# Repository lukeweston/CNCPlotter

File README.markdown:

CNCPlotter

The Freetronics CNCPlotter board is an Arduino-compatible embedded machine which incorporates two bipolar stepper motor drivers, suitable for CNC experiments and other
robotics and mechatronics applications.

The board incorporates the following hardware features:
 
- Atmel ATmega32U4 microcontroller, compatible with the Arduino Leonardo firmware, and USB connectivity to the PC. 
- 20x4 HD44780-compatible alphanumeric LCD display 
- Micro-SD card socket, for example usable for the execution of stored programs without connection to a PC. 
- Connector for a small (hobby RC aircraft style) servo motor 
- Two onboard DRV8811 bipolar stepper motor driver ICs 
- Inputs for three "limit" or "home" switches (or switches with any other kind of software-defined functionality!) 
- Connector for a cheap 4-wire resistive touchscreen, such as a Nintendo DS compatible touchscreen 
- Power supply input voltage range of 9-30V. (At least 1A current capacity is required to run the stepper motors.) 
- Output header for an optional third stepper motor driver IC, enabling three-axis CNC applications. 

Assuming you're using an Arduino Leonardo bootloader, the following is the mapping of Arduino pins to hardware functions.	

D0: UART RXD (not used, broken out to spare header) 	
D1: UART TXD (not used, broken out to spare header) 	
D2: LCD Strobe (Data loaded serially from AVR into 8-bit latch. Same as Pebble LCD hardware.) 	
D3: LCD Data 	
D4: LCD Clock 	
D5: Z-axis direction (not used in most cases) 	
D6: SD Card SPI chip select (active low). Standard SPI hardware (MOSI, MISO, SCK) used for SPI communications with SD card. 	
D7: Z-axis limit switch input (not used in most cases) 	
D8: Y-axis step signal 	
D9: Y-axis direction signal 	
D10: X-axis step signal 	
D11: X-axis direction signal 	
D12: Servo motor PWM position signal 	
D13: Z-axis step signal (not used usually) 	

A0: Touchscreen 1 	
A1: Touchscreen 2 	
A2: Touchscreen 3 	
A3: Touchscreen 4 	
A4: Y-axis limit switch input 	
A5: X-axis limit switch input

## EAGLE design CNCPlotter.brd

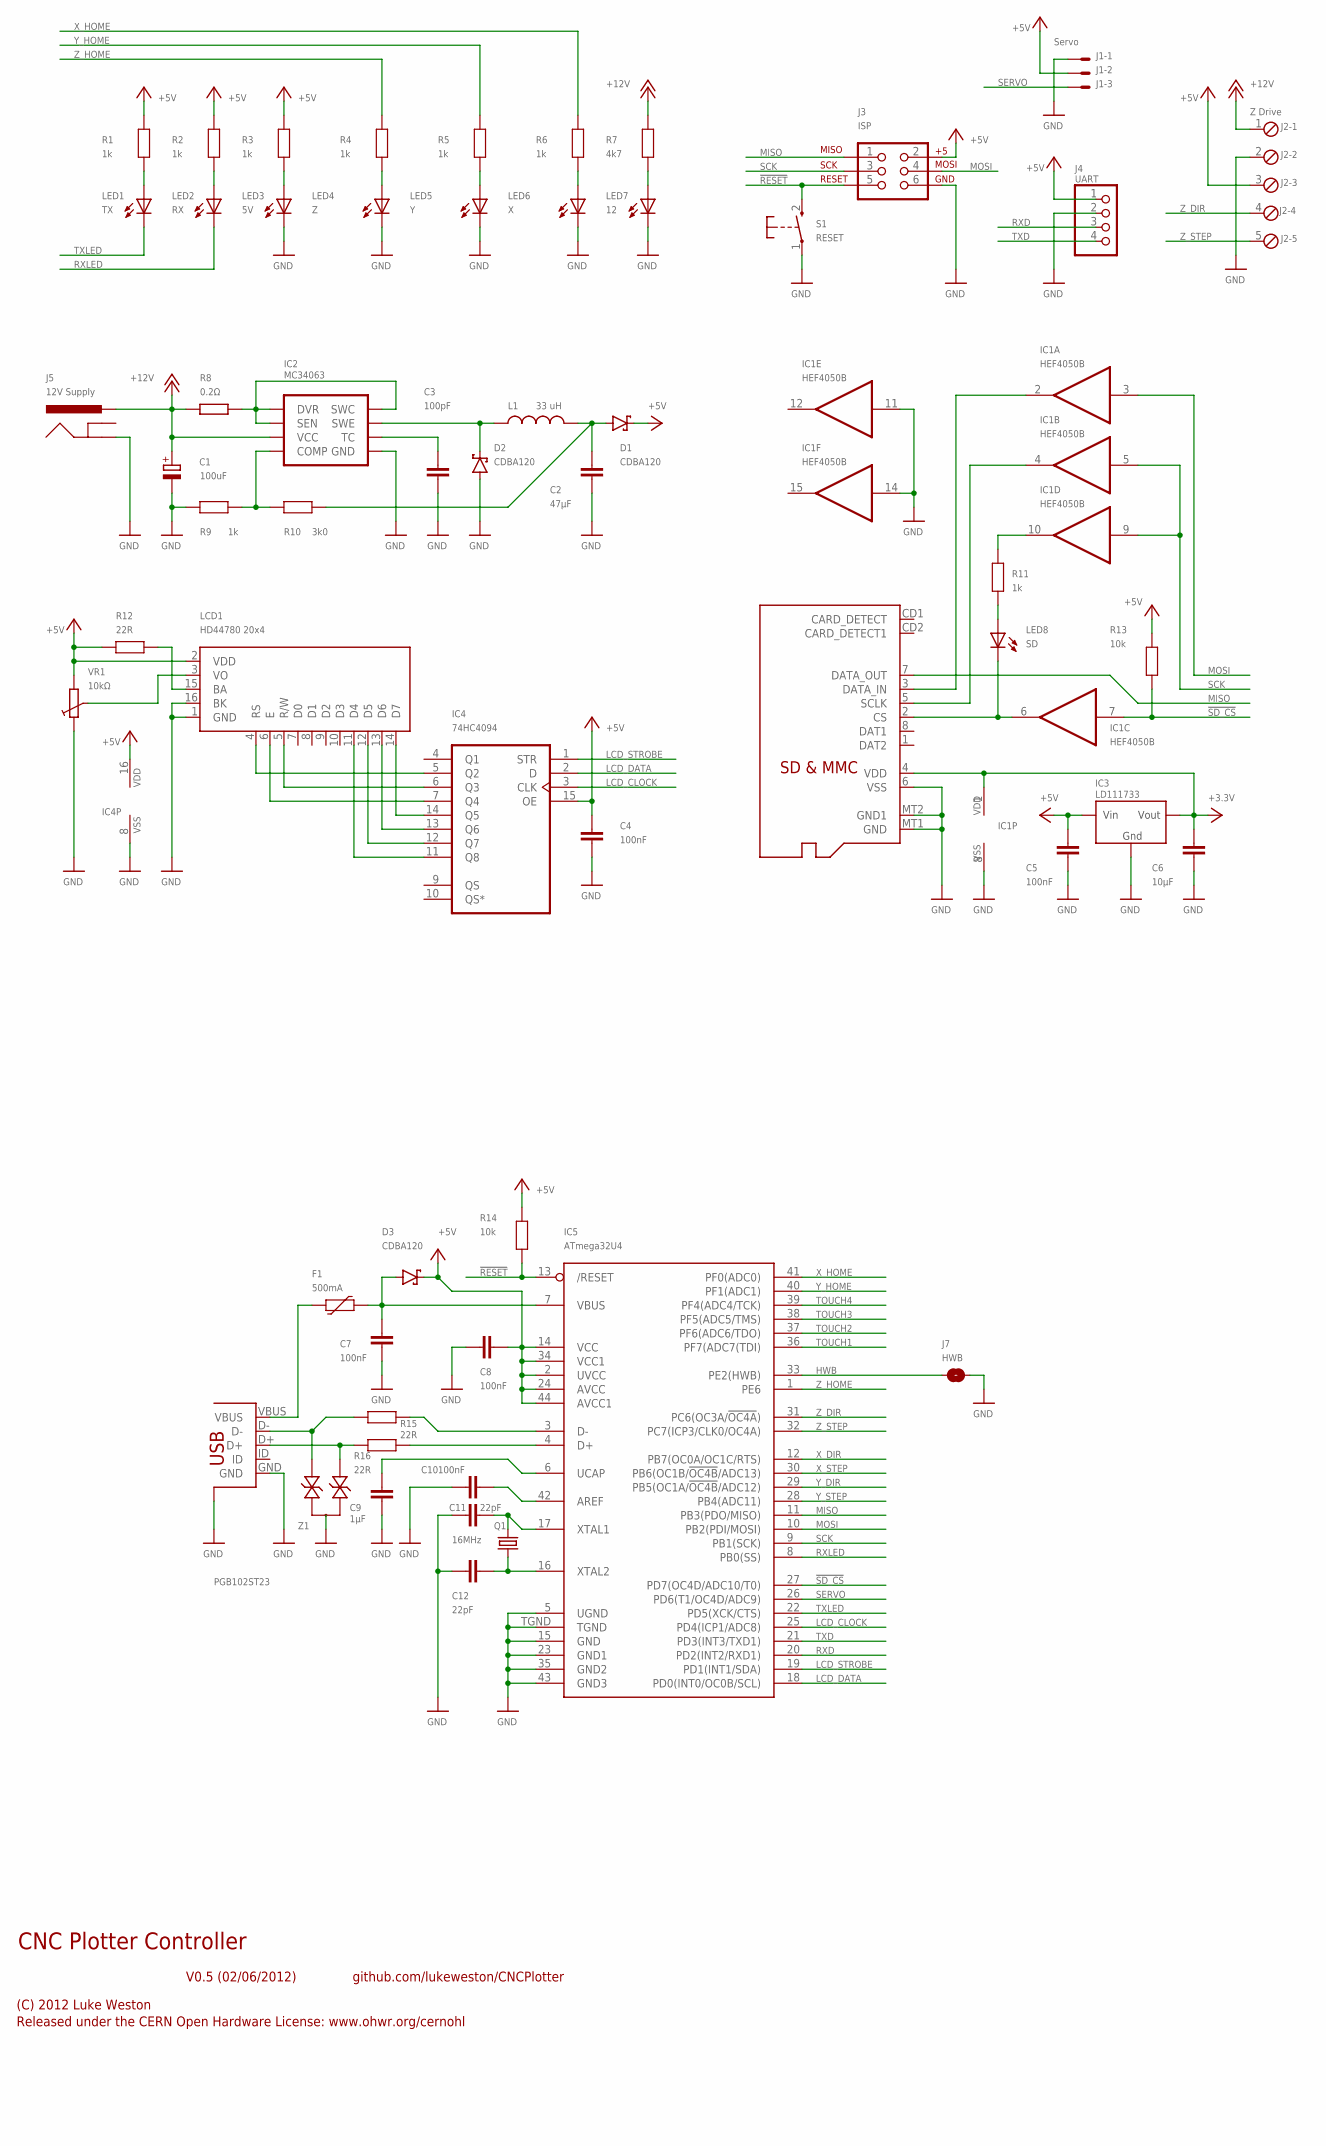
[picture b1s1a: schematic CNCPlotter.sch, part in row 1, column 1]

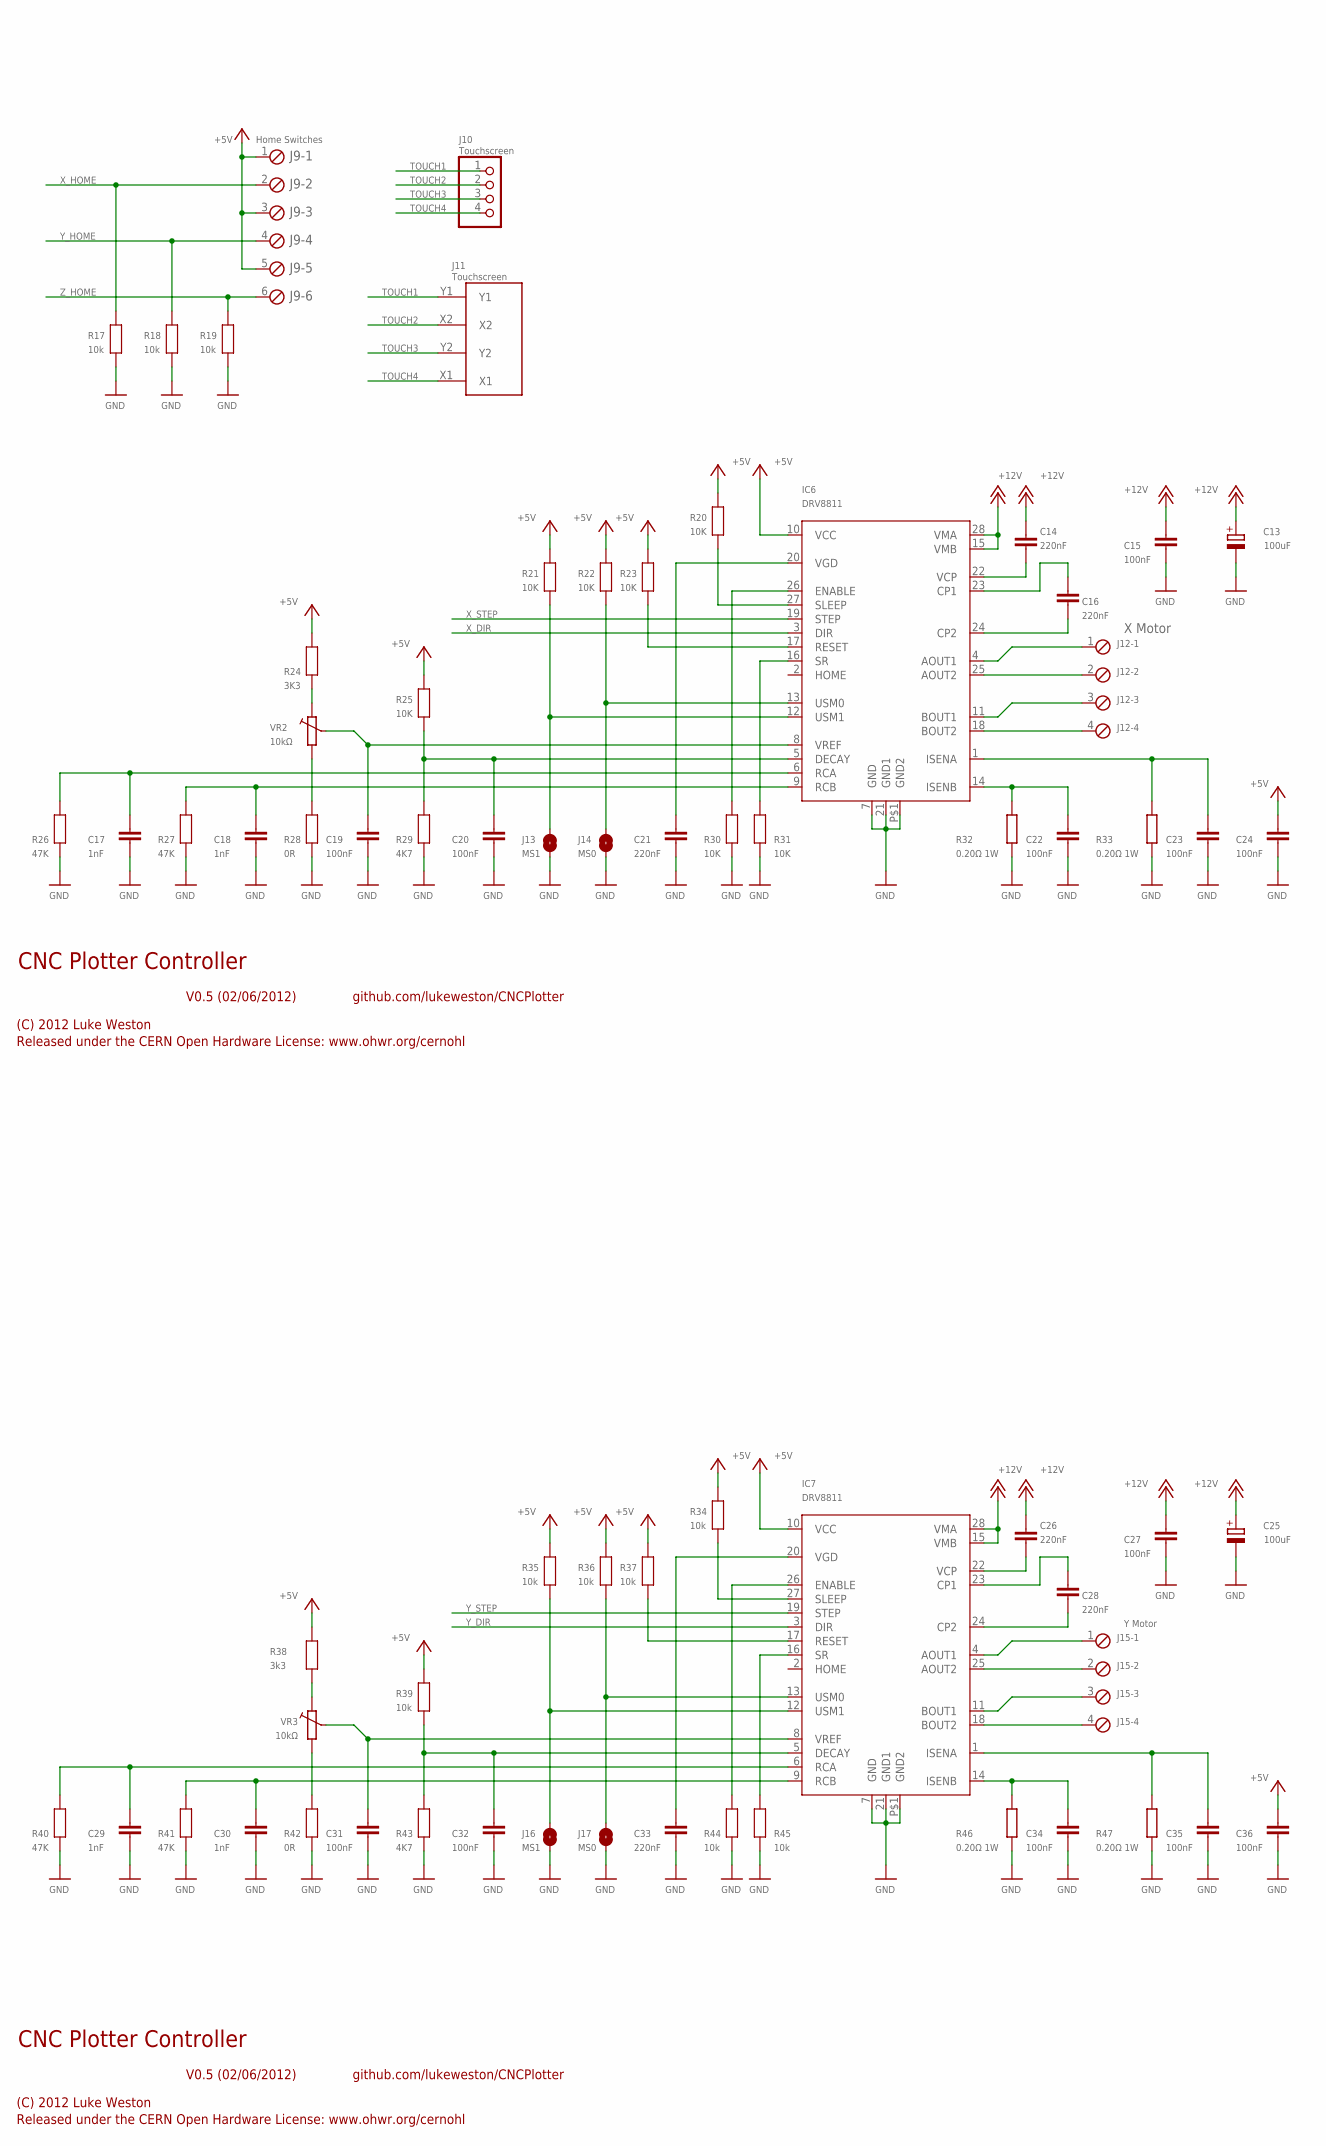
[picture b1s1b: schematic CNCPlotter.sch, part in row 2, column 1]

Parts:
C1, C13, C25: 100uF; E2,5-6
C2: 47µF; C1210
C3: 100pF; 0603
C4, C5, C7, C8, C10, C15, C19, C20, C22, C23, C24, C27, C31, C32, C34, C35, C36: 100nF; 0603
C6: 10µF; 0805
C9: 1µF; 0603
C11, C12: 22pF; 0603
C14, C16, C21, C26, C28, C33: 220nF; 0603
C17, C18, C29, C30: 1nF; 0603
D1, D2, D3: CDBA120; SMA
F1: 500mA; 1812
IC1: HEF4050B; SO16
IC2: MC34063; SO08
IC3: LD111733; SOT223
IC4: 74HC4094; SO16@1
IC5: ATmega32U4; QFN-44N
IC6, IC7: DRV8811; HTSSOP28
J1: Servo; 22-23-2031
J2: Z Drive; 5POL254
J3: ISP; 2X3-NS
J4: UART; 1X04
J5: 12V Supply; POWER_JACK_SLOT
J6: MicroSD Card; ADAFRUIT_MICROSD
J7: HWB; SJ
J8: USB; USB-MINIB-FT
J9: Home Switches; 6POL254
J10: Touchscreen; 1X04
J11: Touchscreen; DS_TOUCH_CONNECTOR
J12: X Motor; 4POL254
J13, J16: MS1; SJ
J14, J17: MS0; SJ
J15: Y Motor; 4POL254
L1: 33 uH; CR75
LCD1: HD44780 20x4; HDM20416L
LED1: TX; LED-0603
LED2: RX; LED-0603
LED3: 5V; LED-0603
LED4: Z; LED-0603
LED5: Y; LED-0603
LED6: X; LED-0603
LED7: 12; LED-0603
LED8: SD; LED-0603
Q1: 16MHz; HC49US
R1, R2, R3, R4, R5, R6, R9, R11: 1k; 0603
R7: 4k7; 0603
R8: 0.2Ω; R1210
R10: 3k0; 0603
R12, R15, R16: 22R; 0603
R13, R14, R17, R18, R19, R34, R35, R36, R37, R39, R44, R45: 10k; 0603
R20, R21, R22, R23, R25, R30, R31: 10K; 0603
R24: 3K3; 0603
R26, R27, R40, R41: 47K; 0603
R28, R42: 0R; 0603
R29, R43: 4K7; 0603
R32, R33, R46, R47: 0.20Ω 1W; R2010
R38: 3k3; 0603
S1: RESET; TACTILE_SWITCH_SMD_2PIN_TINY
VR1, VR2, VR3: 10kΩ; CT6
Z1: PGB102ST23; SOT23-3

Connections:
!RESET: IC5.13 (/RESET), J3.5, R14.1, S1.2 (S)
!SD_CS: IC1.7 (I), IC5.27 (PD7(OC4D/ADC10/T0)), R13.1
+5V: C4.1, C5.1, C8.2, C24.1, C36.1, D1.K, D3.K, IC3.3 (VIN), IC4.15 (OE), IC4.16 (VDD), IC5.2 (UVCC), IC5.14 (VCC), IC5.24 (AVCC), IC5.34 (VCC1), IC5.44 (AVCC1), IC6.10 (VCC), IC7.10 (VCC), J1.2, J2.3, J3.2, J4.1, J9.1, J9.3, J9.5, LCD1.2 (VDD), R1.2, R2.2, R3.2, R12.2, R13.2, R14.2, R20.2, R21.2, R22.2, R23.2, R24.2, R25.2, R34.2, R35.2, R36.2, R37.2, R38.2, R39.2, VR1.A
+12V: C1.+, C13.+, C14.1, C15.1, C25.+, C26.1, C27.1, IC2.6 (VCC), IC6.15 (VMB), IC6.28 (VMA), IC7.15 (VMB), IC7.28 (VMA), J2.1, J5.PWR, R7.2, R8.1
FOO: IC1.6 (O), J6.2 (CS), LED8.C
GND: C1.-, C2.2, C3.2, C4.2, C5.2, C6.2, C7.2, C8.1, C9.1, C10.1, C11.1, C12.1, C13.-, C15.2, C17.2, C18.2, C19.2, C20.2, C21.2, C22.2, C23.2, C24.2, C25.-, C27.2, C29.2, C30.2, C31.2, C32.2, C33.2, C34.2, C35.2, C36.2, D2.A, IC1.8 (VSS), IC1.11 (I), IC1.14 (I), IC2.4 (GND), IC3.1 (GND), IC4.8 (VSS), IC5.5 (UGND), IC5.15 (GND), IC5.23 (GND1), IC5.35 (GND2), IC5.43 (GND3), IC5.TGND, IC6.7 (GND), IC6.21 (GND1), IC6.P$1 (GND2), IC7.7 (GND), IC7.21 (GND1), IC7.P$1 (GND2), J1.1, J2.2, J3.6, J4.2, J5.GND, J6.6 (VSS), J6.MT1 (GND), J6.MT2 (GND1), J7.1, J8.GND, J8.SH1 (SH$1), J8.SH2 (SH$1), J8.SH3 (SH$1), J8.SH4 (SH$1), J13.1, J14.1, J16.1, J17.1, LCD1.1 (GND), LCD1.16 (BK), LED3.C, LED4.C, LED5.C, LED6.C, LED7.C, R9.2, R17.2, R18.2, R19.2, R26.1, R27.1, R28.1, R29.1, R30.1, R31.1, R32.1, R33.1, R40.1, R41.1, R42.1, R43.1, R44.1, R45.1, R46.1, R47.1, S1.1, VR1.E, Z1.3
HWB: IC5.33 (PE2(HWB)), J7.2
LCD_CLOCK: IC4.3 (CLK), IC5.25 (PD4(ICP1/ADC8))
LCD_DATA: IC4.2 (D), IC5.18 (PD0(INT0/OC0B/SCL))
LCD_STROBE: IC4.1 (STR), IC5.19 (PD1(INT1/SDA))
MISO: IC5.11 (PB3(PDO/MISO)), J3.1, J6.7 (DATA_OUT)
MOSI: IC1.3 (I), IC5.10 (PB2(PDI/MOSI)), J3.4
MOSI_3.3V: IC1.2 (O), J6.3 (DATA_IN)
unnamed: IC7.4 (AOUT1), J15.1
unnamed: F1.1, J8.VBUS
unnamed: IC6.4 (AOUT1), J12.1
unnamed: IC7.18 (BOUT2), J15.4
unnamed: IC7.11 (BOUT1), J15.3
unnamed: IC7.25 (AOUT2), J15.2
unnamed: C28.2, IC7.24 (CP2)
unnamed: C28.1, IC7.23 (CP1)
unnamed: C26.2, IC7.22 (VCP)
unnamed: C33.1, IC7.20 (VGD)
unnamed: C10.2, IC5.42 (AREF)
unnamed: LED4.A, R4.1
unnamed: C35.1, IC7.1 (ISENA), R47.2
unnamed: C34.1, IC7.14 (ISENB), R46.2
unnamed: C32.1, IC7.5 (DECAY), R39.1, R43.2
unnamed: C29.1, IC7.6 (RCA), R40.2
unnamed: C16.2, IC6.24 (CP2)
unnamed: C16.1, IC6.23 (CP1)
unnamed: IC6.16 (SR), R31.2
unnamed: C30.1, IC7.9 (RCB), R41.2
unnamed: IC6.18 (BOUT2), J12.4
unnamed: IC6.11 (BOUT1), J12.3
unnamed: IC6.25 (AOUT2), J12.2
unnamed: C14.2, IC6.22 (VCP)
unnamed: C20.1, IC6.5 (DECAY), R25.1, R29.2
unnamed: C21.1, IC6.20 (VGD)
unnamed: C17.1, IC6.6 (RCA), R26.2
unnamed: C9.2, IC5.6 (UCAP)
unnamed: LED3.A, R3.1
unnamed: LED2.A, R2.1
unnamed: LED1.A, R1.1
unnamed: IC2.1 (SWC), IC2.7 (SEN), IC2.8 (DVR), R8.2
unnamed: J8.D+, R16.2, Z1.1
unnamed: J8.D-, R15.2, Z1.2
unnamed: C11.2, IC5.17 (XTAL1), Q1.2
unnamed: C12.2, IC5.16 (XTAL2), Q1.1
unnamed: IC5.4 (D+), R16.1
unnamed: IC5.3 (D-), R15.1
unnamed: LED5.A, R5.1
unnamed: C7.1, D3.A, F1.2, IC5.7 (VBUS)
unnamed: LED6.A, R6.1
unnamed: LED7.A, R7.1
unnamed: C3.1, IC2.3 (TC)
unnamed: IC2.5 (COMP), R9.1, R10.2
unnamed: D2.K, IC2.2 (SWE), L1.P$1 (1)
unnamed: C23.1, IC6.1 (ISENA), R33.2
unnamed: C22.1, IC6.14 (ISENB), R32.2
unnamed: C18.1, IC6.9 (RCB), R27.2
unnamed: IC6.27 (SLEEP), R20.1
unnamed: IC4.5 (Q2), LCD1.4 (RS)
unnamed: IC4.6 (Q3), LCD1.5 (R/W)
unnamed: IC4.7 (Q4), LCD1.6 (E)
unnamed: IC4.11 (Q8), LCD1.11 (D4)
unnamed: IC4.12 (Q7), LCD1.12 (D5)
unnamed: IC4.13 (Q6), LCD1.13 (D6)
unnamed: IC4.14 (Q5), LCD1.14 (D7)
unnamed: IC6.17 (RESET), R23.1
unnamed: LCD1.3 (VO), VR1.S
unnamed: LCD1.15 (BA), R12.1
unnamed: R24.1, VR2.E
unnamed: R28.2, VR2.A
unnamed: LED8.A, R11.1
unnamed: IC1.10 (O), R11.2
unnamed: C19.1, IC6.8 (VREF), VR2.S
unnamed: IC6.26 (ENABLE), R30.2
unnamed: IC6.12 (USM1), J13.2, R21.1
unnamed: IC6.13 (USM0), J14.2, R22.1
unnamed: IC7.27 (SLEEP), R34.1
unnamed: IC7.17 (RESET), R37.1
unnamed: R38.1, VR3.E
unnamed: R42.2, VR3.A
unnamed: C31.1, IC7.8 (VREF), VR3.S
unnamed: IC7.26 (ENABLE), R44.2
unnamed: IC7.12 (USM1), J16.2, R35.1
unnamed: IC7.13 (USM0), J17.2, R36.1
unnamed: IC7.16 (SR), R45.2
REG_5V: C2.1, D1.A, L1.P$2 (2), R10.1
RXD: IC5.20 (PD2(INT2/RXD1)), J4.3
RXLED: IC5.8 (PB0(SS)), LED2.C
SCK: IC1.5 (I), IC1.9 (I), IC5.9 (PB1(SCK)), J3.3
SCK_3.3V: IC1.4 (O), J6.5 (SCLK)
SERVO: IC5.26 (PD6(T1/OC4D/ADC9)), J1.3
TOUCH1: IC5.36 (PF7(ADC7(TDI)), J10.1, J11.Y1
TOUCH2: IC5.37 (PF6(ADC6/TDO)), J10.2, J11.X2
TOUCH3: IC5.38 (PF5(ADC5/TMS)), J10.3, J11.Y2
TOUCH4: IC5.39 (PF4(ADC4/TCK)), J10.4, J11.X1
TXD: IC5.21 (PD3(INT3/TXD1)), J4.4
TXLED: IC5.22 (PD5(XCK/CTS)), LED1.C
VDD: C6.1, IC1.1 (VDD), IC3.2 (VOUT), J6.4 (VDD)
X_DIR: IC5.12 (PB7(OC0A/OC1C/RTS)), IC6.3 (DIR)
X_HOME: IC5.41 (PF0(ADC0)), J9.2, R6.2, R17.1
X_STEP: IC5.30 (PB6(OC1B/!OC4B!/ADC13)), IC6.19 (STEP)
Y_DIR: IC5.29 (PB5(OC1A/!OC4B!/ADC12)), IC7.3 (DIR)
Y_HOME: IC5.40 (PF1(ADC1)), J9.4, R5.2, R18.1
Y_STEP: IC5.28 (PB4(ADC11)), IC7.19 (STEP)
Z_DIR: IC5.31 (PC6(OC3A/!OC4A!)), J2.4
Z_HOME: IC5.1 (PE6), J9.6, R4.2, R19.1
Z_STEP: IC5.32 (PC7(ICP3/CLK0/OC4A)), J2.5

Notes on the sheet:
CNC Plotter Controller
V0.5 (02/06/2012)
(C) 2012 Luke Weston
Released under the CERN Open Hardware License: www.ohwr.org/cernohl
github.com/lukeweston/CNCPlotter

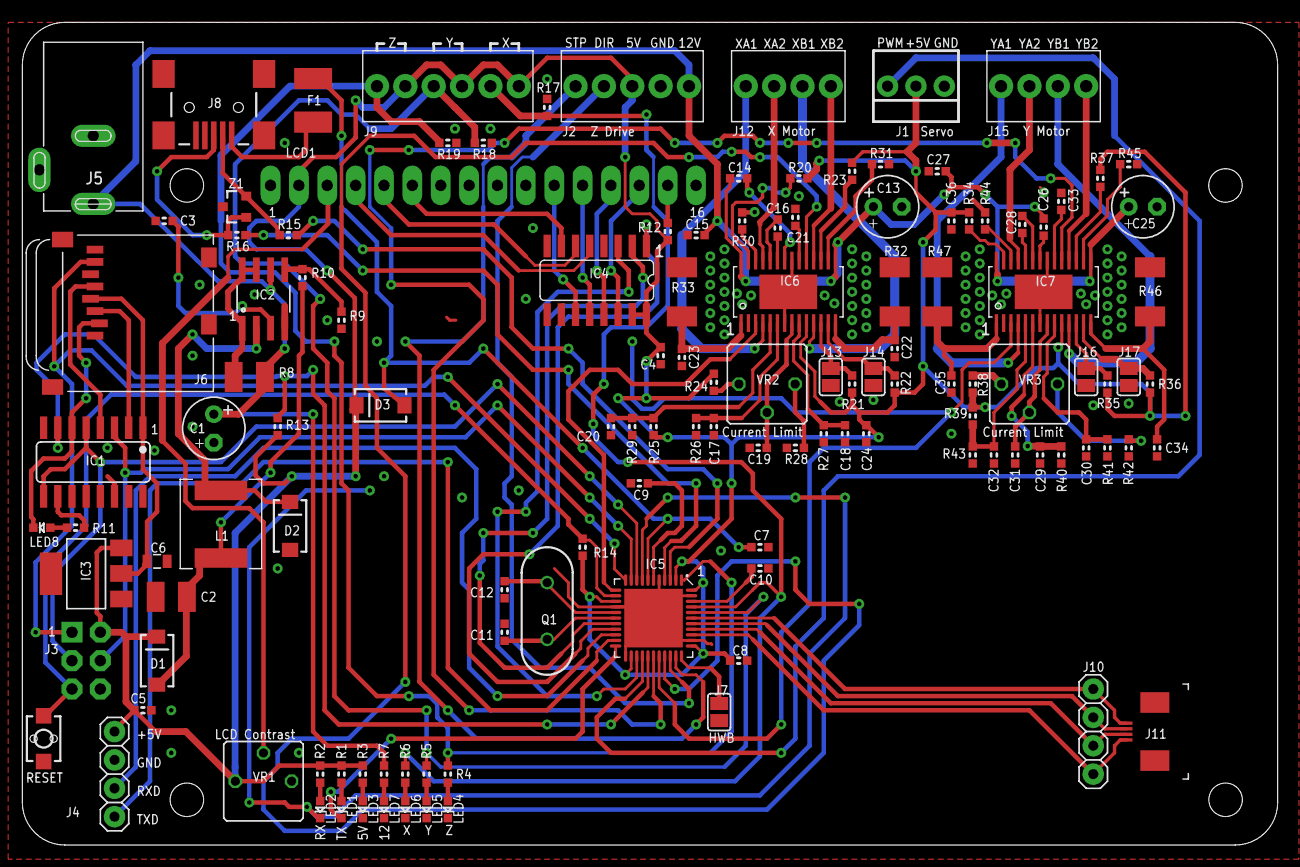
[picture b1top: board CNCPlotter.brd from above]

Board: 2 copper layers, 112.4 x 73.7 mm, 127 parts (0 on the bottom side), 111 nets.

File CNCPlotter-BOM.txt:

R1, R2, R3, R4, R5, R6, R9, R11:								1k0, 0.1W, 0603 SMD, 5%
R13, R14, R17, R18, R19, R20, R21, R22, R23, R25, R30, R31, R34, R35, R36, R37, R39, R44, R45:	10k, 0.1W, 0603 SMD, 5%

R10:			3k0, 0.1W, 0603 SMD, 1%
R24, R38:		3k3, 0.1W, 0603 SMD, 5%
R12, R15, R16:		22R, 0.1W, 0603 SMD, 5%
R26, R27, R40, R41:	47k, 0.1W, 0603 SMD, 5%
R7, R29, R43:		4k7, 0.1W, 0603 SMD, 5%
R28, R42:		0 ohm, 0603 SMD
R8:			0.20 ohms, 0.5W, 1210 SMD, 5%. Eg. Digi-Key 73L5R20JCT-ND
R32, R33, R46, R47:	0.20 ohms, 1W, 2010 SMD, 1%. Eg. Digi-Key CSRN2010FKR200CT-ND

VR1, VR2, VR3:		CT6EP103 10k trimpot, eg. Digi-Key CT6EP103-ND

C1, C13, C25:		100 uF 35V Al electrolytic, through-hole, 2.5mm lead pitch / 6mm diameter. Eg. Digi-Key 399-6104-ND
C2:			47 uF ceramic, 1210 SMD. Eg. Digi-Key 445-1409-1-ND
C6:			10uF ceramic, 0805 SMD. Eg. Digi-Key 445-1371-1-ND
C3:			100 pF ceramic, 0603 SMD.
C9:			1 uF ceramic, 0603 SMD.
C11, C12:		22 pF ceramic, 0603 SMD.
C17, C18, C29, C30:	1 nF ceramic, 0603 SMD.

C14, C16, C21, C26, C28, C33:	220nF ceramic, 0603 SMD
C4, C5, C7, C8, C10, C15, C19, C20, C22, C23, C24, C27, C31, C32, C34, C35, C36: 100nF ceramic, 0603 SMD

D1, D2, D3:	CDBA120 Schottky diode, SMA package. Eg. Digi-Key 641-1014-1-ND
Z1:		PGB102ST23 ESD supressor, eg. Digi-Key F2596CT-ND 
Q1:		16 MHz crystal, through-hole HC-49US. Eg. Digi-Key 631-1108-ND
L1:		CR75 33uH power inductor, eg. Digi-Key 308-1539-1-ND
F1:		500mA PPTC, 1812 SMD package. Eg. Digi-Key 507-1361-1-ND

IC1:		MC14050, 16-SOIC package. Eg. Digi-Key MC14050BDGOS-ND
IC2:		MC34063 switching regulator, 8-SOIC package. Eg. Digi-Key 497-7852-1-ND
IC3:		LD1117S33C 3.3V regulator, SOT-223 package. Eg. Digi-Key 497-1241-1-ND
IC4:		74HC4094 shift register, 16-SOIC package. Eg. Digi-Key 568-1465-5-ND
IC5:		ATmega32U4 AVR microcontroller, 44-QFN package. Eg. Digi-Key ATMEGA32U4-MU-ND
IC6, IC7:	DRV8811 stepper motor driver, 28-HTSSOP. Eg. Digi-Key 296-24591-1-ND

LED1, LED7:		LED, green, 0603 SMD.
LED2, LED8:		LED, yellow, 0603 SMD.
LED3:			LED, blue, 0603 SMD.
LED4, LED5, LED6:	LED, red, 0603 SMD.

J1:		3-pin 0.1" pin header
J3:		2x3 0.1" pin header
J2:		5-pin 0.1" PCB-mount screw terminal block, eg. Digi-Key A98336-ND
J5:		2.1mm DC power jack, eg. Digi-Key CP-037A-ND
J6:		Micro-SD card socket, eg. Digi-Key 101-00660-68-6-1-ND
J8:		USB Mini-B socket, eg. Digi-Key H2959CT-ND
J9:		6-pin 0.1" PCB-mount screw terminal block, eg. Digi-Key A98337-ND
J11: 		4-pin 0.5mm SMD FFC ribbon connector, eg. Digi-Key 609-4328-1-ND
J12, J15:	4-pin 0.1" PCB-mount screw terminal block, eg. Digi-Key A98335-ND
J4:		NOT PLACED.
J10: 		NOT PLACED.

LCD1:		20x4 HD44780-compatible backlit LCD display module.
Same as Pebble, RAMPS Display Board, etc etc.
Also include appropriate headers (16-pin single-row 0.1", mating male/female pair) for LCD.

Also needed: 12V plugpack.

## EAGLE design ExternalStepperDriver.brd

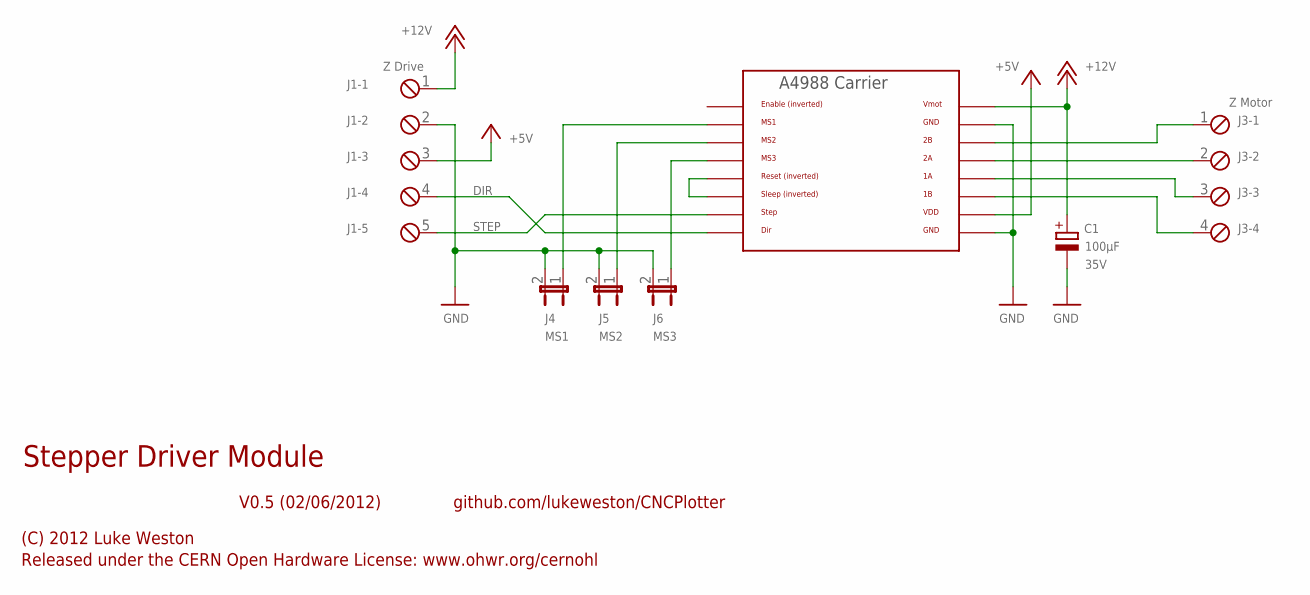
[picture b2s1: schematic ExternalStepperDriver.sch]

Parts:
C1: 100µF; E2,5-6; VOLTAGE 35V
J1: Z Drive; 5POL254
J2: A4988BREAKOUT
J3: Z Motor; 4POL254
J4: MS1; JP1
J5: MS2; JP1
J6: MS3; JP1

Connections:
+5V: J1.3, J2.VDD
+12V: C1.+, J1.1, J2.VMOT
DIR: J1.4, J2.DIR
GND: C1.-, J1.2, J2.GND, J2.GND@0 (GND), J4.2, J5.2, J6.2
unnamed: J2.MS1, J4.1
unnamed: J2.MS2, J5.1
unnamed: J2.MS3, J6.1
unnamed: J2.RST, J2.SLP (SLEEP)
unnamed: J2.2B, J3.1
unnamed: J2.1B, J3.4
unnamed: J2.1A, J3.3
unnamed: J2.2A, J3.2
STEP: J1.5, J2.STEP

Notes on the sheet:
Stepper Driver Module
V0.5 (02/06/2012)
(C) 2012 Luke Weston
Released under the CERN Open Hardware License: www.ohwr.org/cernohl
github.com/lukeweston/CNCPlotter

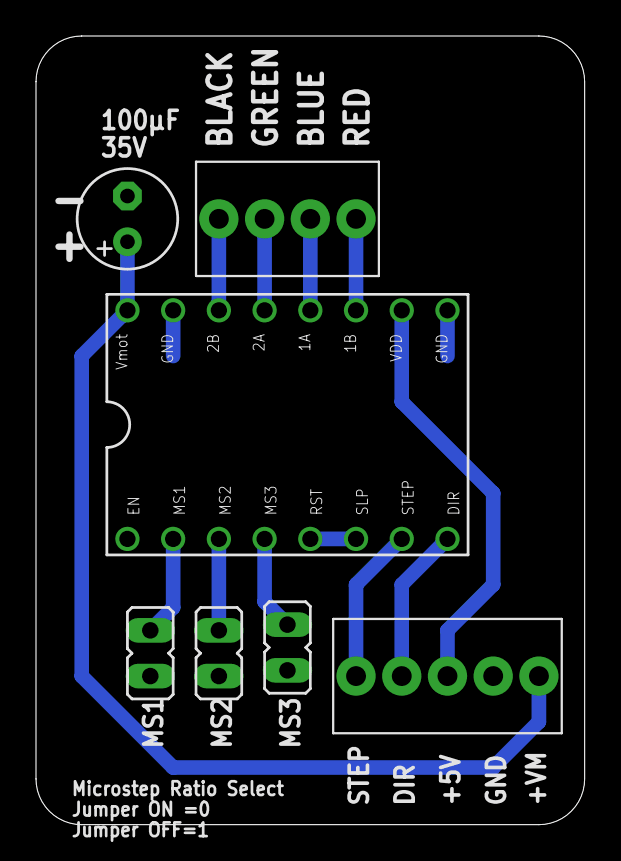
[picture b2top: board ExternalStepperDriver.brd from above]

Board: 2 copper layers, 30.5 x 43.8 mm, 7 parts (0 on the bottom side), 13 nets.

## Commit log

2012-10-04 added BOM
2012-10-31 added placement overlays
2012-11-13 added external stepper module
2013-01-05 added reset button
